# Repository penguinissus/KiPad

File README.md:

# KiPad
A macropad built for the most common KiCAD shortcuts. 

# User Instructions
Assembly: 
1. Print out and buy all the parts found in `BOM.csv`
2. Solder everything together
3. Put in the keycaps accordingly (refer to `3d-models/full-assembly.step` or pictures below)
4. Sandwich PCB between the top and the bottom case

Firmware: 
1. go to circuitpython.org/downloads
2. download circuitpython for XIAO RP2040
3. plug in keyboard to laptop and make sure to use a data transmitting cable
4. open up the pico folder in your computer's directory
5. replace the contents of `code.py` in the XIAO RP2040 folder with the one in this repo

# Why did I make it
I wanted to make the process of designing on KiCAD easier, so I made this macropad for this problem. 

# Diagrams
Schematic:  
  
PCB Editor:  
  
PCB Assembly:  
  
Full Assembly:  

# BOM
|Part|Amount|Price (USD)|
|----:|:-----|:------|
|Cherry MX Switches|12|$5.63|
|Keycaps|12 (1 of each design)|$0|
|XIAO RP2040|1|$13.15|
|PCB|1|$2|
|Case (top and bottom)|1 each|$0|

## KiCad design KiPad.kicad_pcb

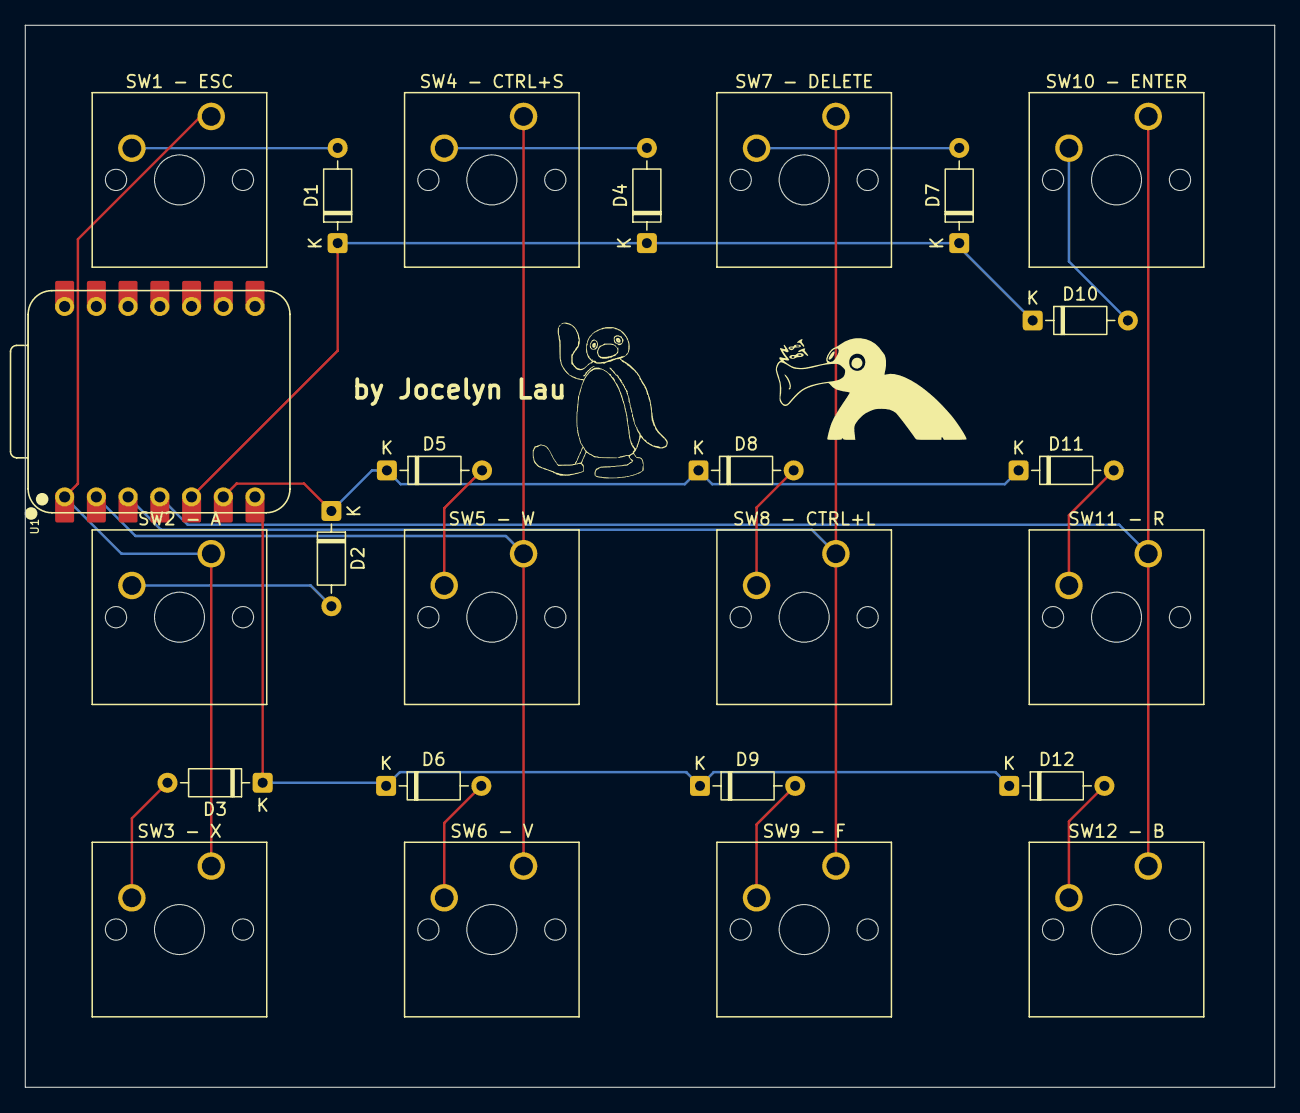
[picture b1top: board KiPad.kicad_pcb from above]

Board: 2 copper layers, 100.0 x 85.0 mm, 25 parts (0 on the bottom side), 19 nets.

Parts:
D1, D2, D3, D4, D5, D6, D7, D8, D9, D10, D11, D12: 1N4148; D_DO-35_SOD27_P7.62mm_Horizontal
SW1 - ESC, SW2 - A, SW3 - X, SW4 - CTRL+S, SW5 - W, SW6 - V, SW7 - DELETE, SW8 - CTRL+L, SW9 - F, SW10 - ENTER, SW11 - R, SW12 - B: SW_Push_45deg; SW_Cherry_MX_1.00u_PCB
U1: XIAO-RP2040-DIP

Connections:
COL1: D1.1 (K), D4.1 (K), D7.1 (K), D10.1 (K), U1.5 (GPIO6/SDA)
COL2: D2.1 (K), D5.1 (K), D8.1 (K), D11.1 (K), U1.6 (GPIO7/SCL)
COL3: D3.1 (K), D6.1 (K), D9.1 (K), D12.1 (K), U1.7 (GPIO0/TX)
unnamed: D1.2 (A), SW1 - ESC.2
unnamed: D2.2 (A), SW2 - A.2
unnamed: D3.2 (A), SW3 - X.2
unnamed: D4.2 (A), SW4 - CTRL+S.2
unnamed: D5.2 (A), SW5 - W.2
unnamed: D6.2 (A), SW6 - V.2
unnamed: D7.2 (A), SW7 - DELETE.2
unnamed: D8.2 (A), SW8 - CTRL+L.2
unnamed: D9.2 (A), SW9 - F.2
unnamed: D10.2 (A), SW10 - ENTER.2
unnamed: D11.2 (A), SW11 - R.2
unnamed: D12.2 (A), SW12 - B.2
ROW1: SW1 - ESC.1, SW2 - A.1, SW3 - X.1, U1.1 (GPIO26/ADC0/A0)
ROW2: SW4 - CTRL+S.1, SW5 - W.1, SW6 - V.1, U1.2 (GPIO27/ADC1/A1)
ROW3: SW7 - DELETE.1, SW8 - CTRL+L.1, SW9 - F.1, U1.3 (GPIO28/ADC2/A2)
ROW4: SW10 - ENTER.1, SW11 - R.1, SW12 - B.1, U1.4 (GPIO29/ADC3/A3)

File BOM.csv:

"Id";"Designator";"Footprint";"Quantity";"Designation";"Supplier and ref";
1;"D1, D2, D3, D4, D5, D6, D7, D8, D9, D10, D11, D12";"D_DO-35_SOD27_P7.62mm_Horizontal";12;"1N4148";;;
2;"SW1 - ESC, SW2 - A, SW3 - X, SW4 - CTRL+S, SW5 - W, SW6 - V, SW7 - DELETE, SW8 - CTRL+L, SW9 - F, SW10 - ENTER, SW11 - R, SW12 - B";"SW_Cherry_MX_1.00u_PCB";12;"SW_Push_45deg";;;
3;"U1";"XIAO-RP2040-DIP";1;"XIAO-RP2040-DIP";;;

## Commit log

2026-06-23 schematic and assigned footprints done
2026-06-23 finished pcb design
2026-06-23 cad models
2026-06-23 code
2026-06-23 readme and zine
2026-06-27 remade model and added production files
2026-06-27 reorganize
